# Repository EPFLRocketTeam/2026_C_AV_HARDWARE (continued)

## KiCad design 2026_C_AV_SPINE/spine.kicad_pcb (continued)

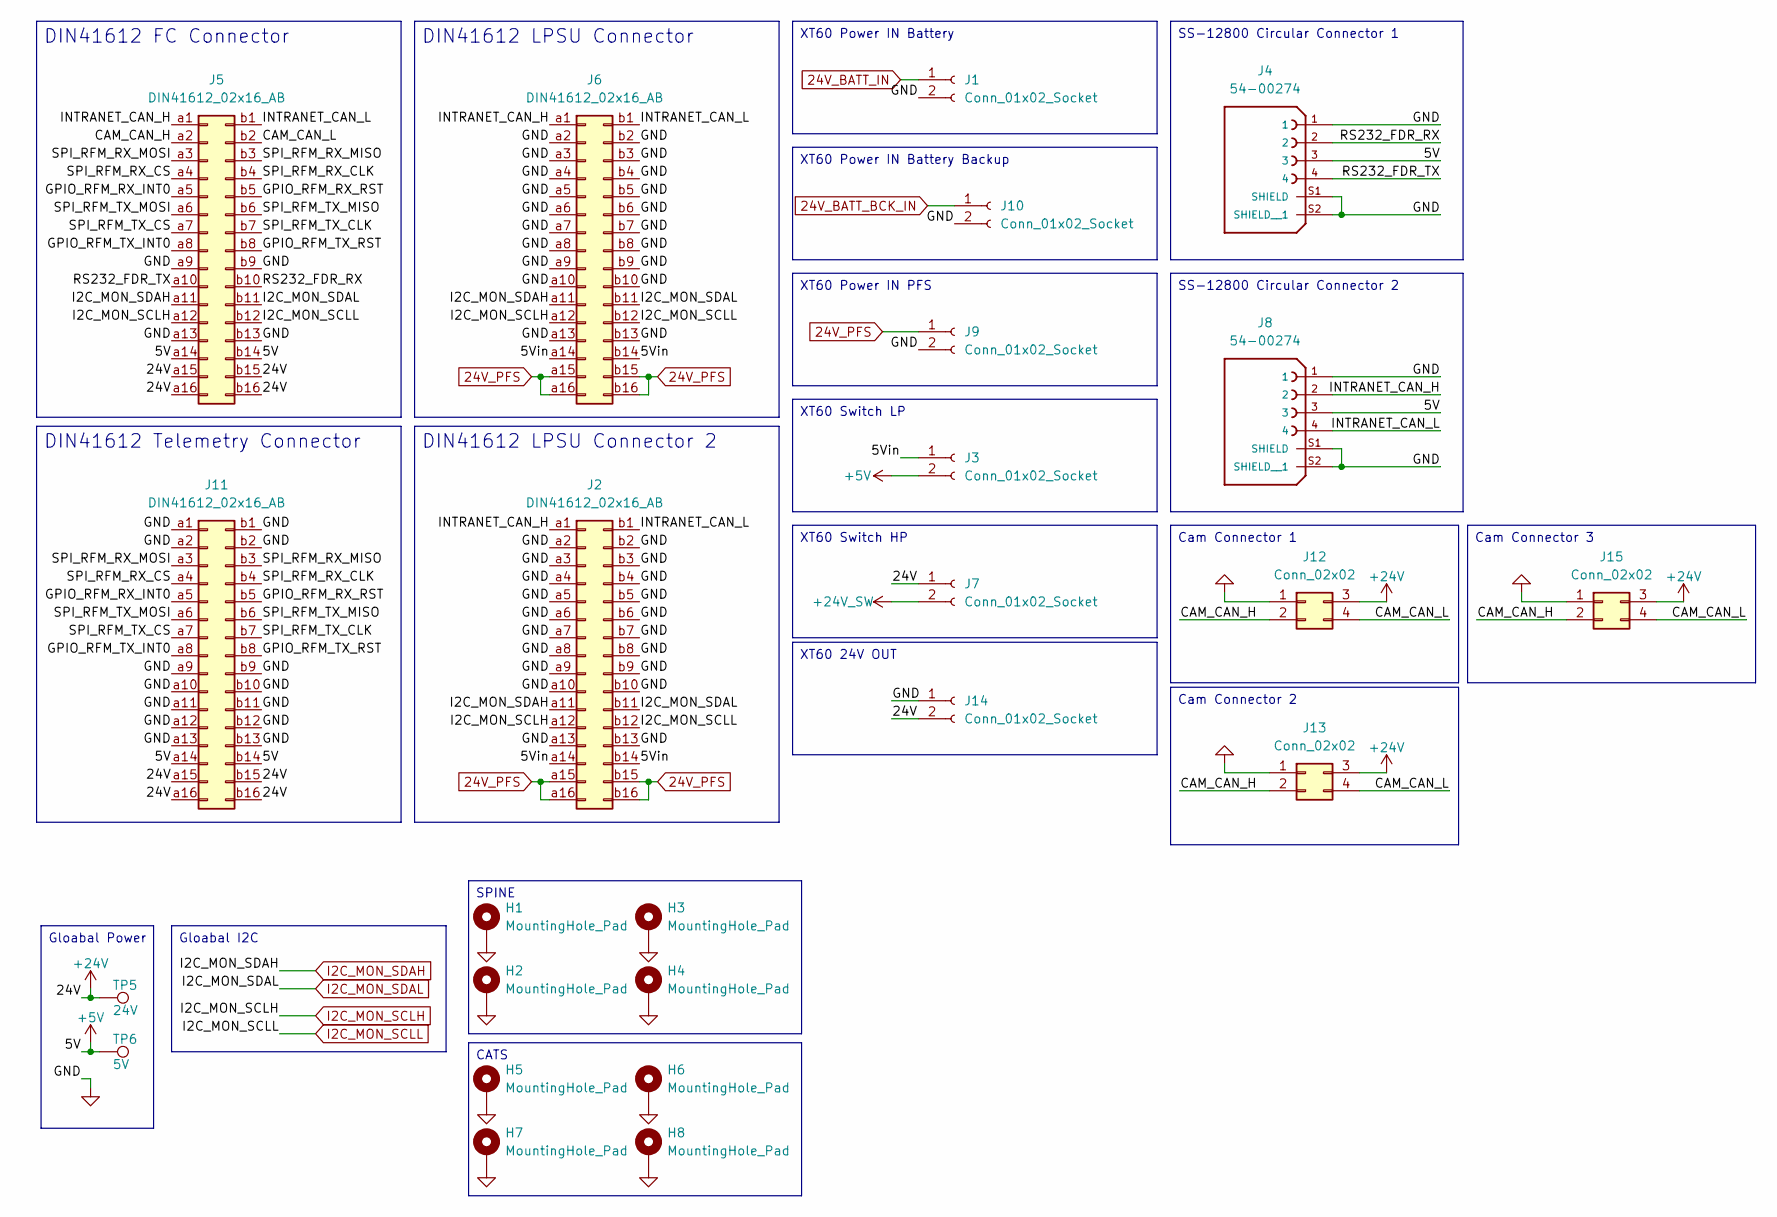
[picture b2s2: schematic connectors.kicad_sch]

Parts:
H1, H2, H3, H4, H5, H6, H7, H8: MountingHole_Pad; MountingHole_3.2mm_M3_Pad
J1, J3, J7, J9, J10, J14: Conn_01x02_Socket; AMASS_XT60IPW-M_1x03_P7.20mm_Horizontal
J2, J5, J6, J11: DIN41612_02x16_AB; DIN41612_B2_2x16_Female_Vertical_THT
J4, J8: 54-00274; TENSILITY_54-00274; PARTREV A
J12, J13, J15: Conn_02x02; SHDRRA4W55P200_2X2_665X640X630P
TP5: 24V; TestPoint_THTPad_D3.0mm_Drill1.5mm
TP6: 5V; TestPoint_THTPad_D3.0mm_Drill1.5mm

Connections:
24V_BATT_BCK_IN: J10.1; also elsewhere on the board
24V_BATT_IN: J1.1; also elsewhere on the board
24V_PFS: J2.a15, J2.a16, J2.b15, J2.b16, J6.a15, J6.a16, J6.b15, J6.b16, J9.1; also elsewhere on the board
+5V: J3.2, J4.3, J5.a14, J5.b14, J8.3, J11.a14, J11.b14, TP6.1; also elsewhere on the board
+24V: J5.a15, J5.a16, J5.b15, J5.b16, J7.1, J11.a15, J11.a16, J11.b15, J11.b16, J12.3, J13.3, J14.2, J15.3, TP5.1
+24V_SW: J7.2; also elsewhere on the board
/Connectors/5Vin: J2.a14, J2.b14, J3.1, J6.a14, J6.b14
/Connectors/CAM_CAN_H: J5.a2, J12.2, J13.2, J15.2
/Connectors/CAM_CAN_L: J5.b2, J12.4, J13.4, J15.4
/Connectors/GPIO_RFM_RX_INT0: J5.a5, J11.a5
/Connectors/GPIO_RFM_RX_RST: J5.b5, J11.b5
/Connectors/GPIO_RFM_TX_INT0: J5.a8, J11.a8
/Connectors/GPIO_RFM_TX_RST: J5.b8, J11.b8
/Connectors/INTRANET_CAN_H: J2.a1, J5.a1, J6.a1, J8.2
/Connectors/INTRANET_CAN_L: J2.b1, J5.b1, J6.b1, J8.4
/Connectors/RS232_FDR_RX: J4.2, J5.b10
/Connectors/RS232_FDR_TX: J4.4, J5.a10
/Connectors/SPI_RFM_RX_CLK: J5.b4, J11.b4
/Connectors/SPI_RFM_RX_CS: J5.a4, J11.a4
/Connectors/SPI_RFM_RX_MISO: J5.b3, J11.b3
/Connectors/SPI_RFM_RX_MOSI: J5.a3, J11.a3
/Connectors/SPI_RFM_TX_CLK: J5.b7, J11.b7
/Connectors/SPI_RFM_TX_CS: J5.a7, J11.a7
/Connectors/SPI_RFM_TX_MISO: J5.b6, J11.b6
/Connectors/SPI_RFM_TX_MOSI: J5.a6, J11.a6
GND: H1.1, H2.1, H3.1, H4.1, H5.1, H6.1, H7.1, H8.1, J1.2, J2.a2, J2.a3, J2.a4, J2.a5, J2.a6, J2.a7, J2.a8, J2.a9, J2.a10, J2.a13, J2.b2, J2.b3, J2.b4, J2.b5, J2.b6, J2.b7, J2.b8, J2.b9, J2.b10, J2.b13, J4.1, J4.S1 (SHIELD), J4.S2 (SHIELD__1), J5.a9, J5.a13, J5.b9, J5.b13, J6.a2, J6.a3, J6.a4, J6.a5, J6.a6, J6.a7, J6.a8, J6.a9, J6.a10, J6.a13, J6.b2, J6.b3, J6.b4, J6.b5, J6.b6, J6.b7, J6.b8, J6.b9, J6.b10, J6.b13, J8.1, J8.S1 (SHIELD), J8.S2 (SHIELD__1), J9.2, J10.2, J11.a1, J11.a2, J11.a9, J11.a10, J11.a11, J11.a12, J11.a13, J11.b1, J11.b2, J11.b9, J11.b10, J11.b11, J11.b12, J11.b13, J12.1, J13.1, J14.1, J15.1; also elsewhere on the board
I2C_MON_SCLH: J2.a12, J5.a12, J6.a12; also elsewhere on the board
I2C_MON_SCLL: J2.b12, J5.b12, J6.b12; also elsewhere on the board
I2C_MON_SDAH: J2.a11, J5.a11, J6.a11; also elsewhere on the board
I2C_MON_SDAL: J2.b11, J5.b11, J6.b11; also elsewhere on the board

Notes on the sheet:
SPINE
XT60 Switch HP
DIN41612 LPSU Connector 2
Cam Connector 3
Cam Connector 1
DIN41612 LPSU Connector
DIN41612 Telemetry Connector
XT60 Power IN Battery Backup
Gloabal I2C
CATS
SS-12800 Circular Connector 2
XT60 24V OUT
SS-12800 Circular Connector 1
DIN41612 FC Connector
XT60 Power IN Battery
Cam Connector 2
XT60 Switch LP
XT60 Power IN PFS
Gloabal Power

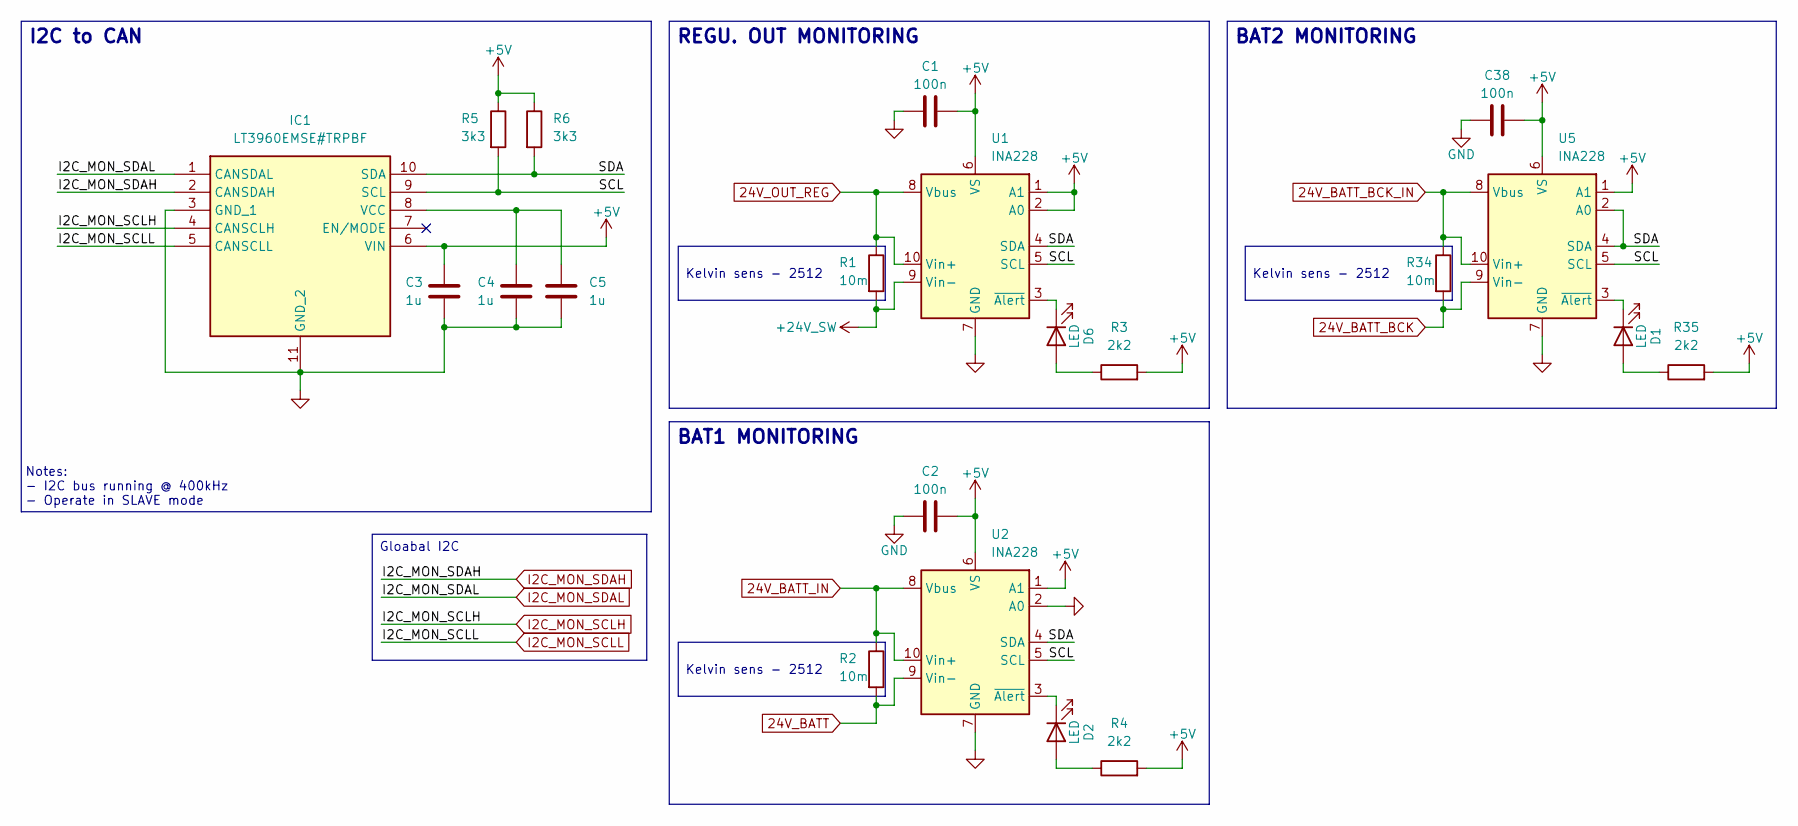
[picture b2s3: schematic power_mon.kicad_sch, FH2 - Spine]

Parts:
C1, C2, C38: 100n; C_0603_1608Metric
C3, C4, C5: 1u; C_0603_1608Metric
D1, D2, D6: LED; LED_0603_1608Metric
IC1: LT3960EMSE#TRPBF; SOP50P490X110-11N; Mouser Part Number 584-LT3960EMSE#TRPBF
R1, R2, R34: 10m; R_2512_6332Metric
R3, R4, R35: 2k2; R_0603_1608Metric
R5, R6: 3k3; R_0603_1608Metric
U1, U2, U5: INA228; VSSOP-10_3x3mm_P0.5mm

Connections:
24V_BATT: R2.2, U2.9 (Vin-); also elsewhere on the board
24V_BATT_BCK: R34.2, U5.9 (Vin-); also elsewhere on the board
24V_BATT_BCK_IN: R34.1, U5.8 (Vbus), U5.10 (Vin+); also elsewhere on the board
24V_BATT_IN: R2.1, U2.8 (Vbus), U2.10 (Vin+); also elsewhere on the board
24V_OUT_REG: R1.1, U1.8 (Vbus), U1.10 (Vin+); also elsewhere on the board
+5V: C1.2, C2.2, C3.1, C38.2, IC1.6 (VIN), R3.2, R4.2, R5.1, R6.1, R35.2, U1.1 (A1), U1.2 (A0), U1.6 (VS), U2.1 (A1), U2.6 (VS), U5.1 (A1), U5.6 (VS); also elsewhere on the board
+24V_SW: R1.2, U1.9 (Vin-); also elsewhere on the board
/Power/Monitoring/SCL: IC1.9 (SCL), R5.2, U1.5 (SCL), U2.5 (SCL), U5.5 (SCL)
/Power/Monitoring/SDA: IC1.10 (SDA), R6.2, U1.4 (SDA), U2.4 (SDA), U5.2 (A0), U5.4 (SDA)
GND: C1.1, C2.1, C3.2, C4.1, C5.2, C38.1, IC1.3 (GND_1), IC1.11 (GND_2), U1.7 (GND), U2.2 (A0), U2.7 (GND), U5.7 (GND); also elsewhere on the board
I2C_MON_SCLH: IC1.4 (CANSCLH); also elsewhere on the board
I2C_MON_SCLL: IC1.5 (CANSCLL); also elsewhere on the board
I2C_MON_SDAH: IC1.2 (CANSDAH); also elsewhere on the board
I2C_MON_SDAL: IC1.1 (CANSDAL); also elsewhere on the board
unnamed: D1.2 (A), R35.1
unnamed: D1.1 (K), U5.3 (~Alert)
unnamed: D2.2 (A), R4.1
unnamed: D2.1 (K), U2.3 (~Alert)
unnamed: D6.2 (A), R3.1
unnamed: D6.1 (K), U1.3 (~Alert)
unnamed: C4.2, C5.1, IC1.8 (VCC)

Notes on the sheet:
Notes: - I2C bus running @ 400kHz - Operate in SLAVE mode
I2C to CAN
BAT2 MONITORING
REGU. OUT MONITORING
Kelvin sens - 2512
BAT1 MONITORING
Gloabal I2C

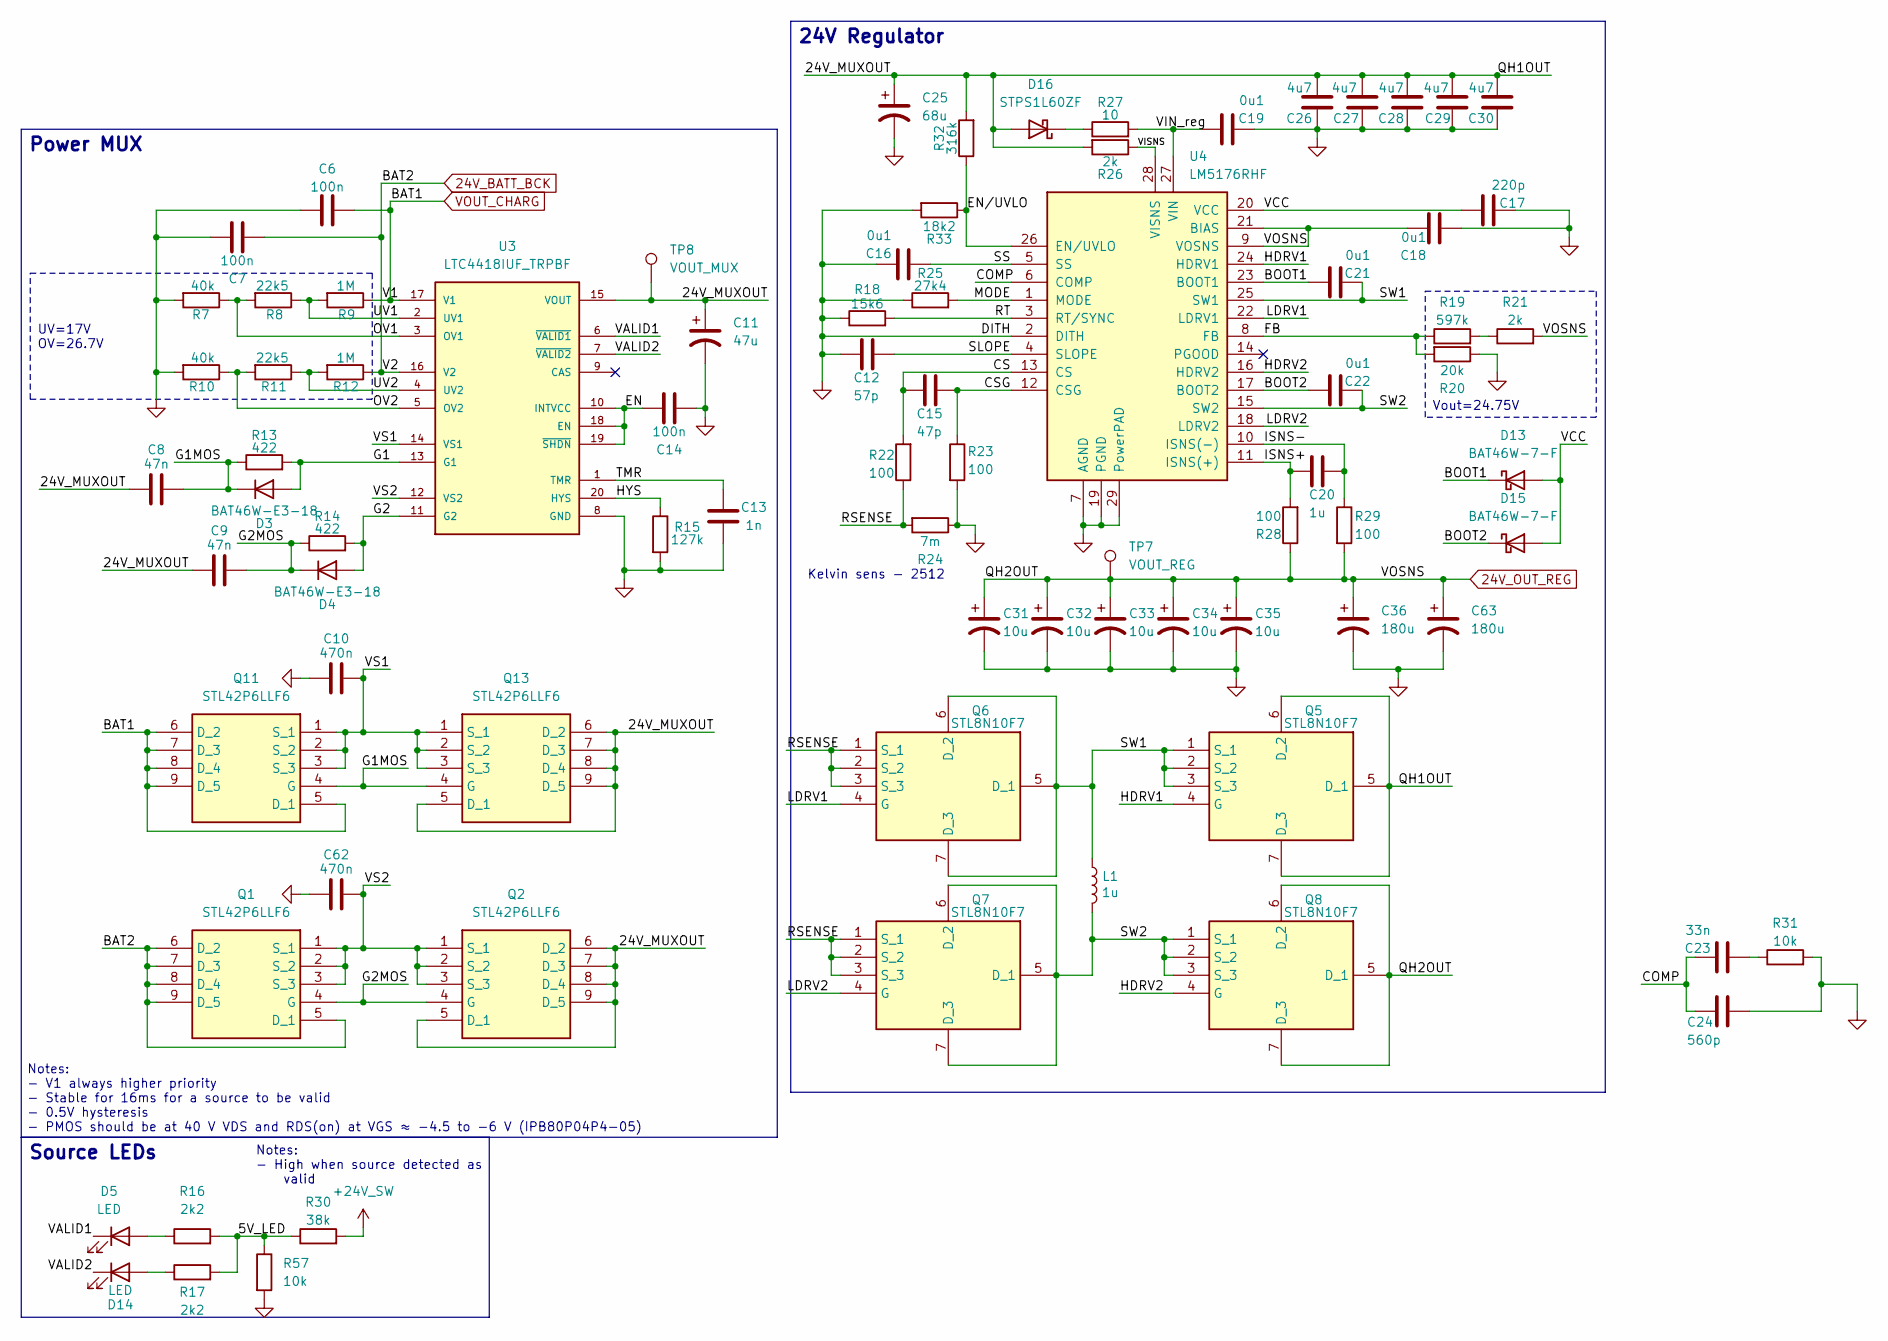
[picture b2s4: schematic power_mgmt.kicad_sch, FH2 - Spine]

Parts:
C6, C7, C14: 100n; C_0603_1608Metric
C8, C9: 47n; C_0603_1608Metric
C10, C62: 470n; C_0603_1608Metric
C11: 47u; CP_Elec_6.3x9.9
C12: 57p; C_0603_1608Metric
C13: 1n; C_0603_1608Metric
C15: 47p; C_0603_1608Metric
C16, C18, C19, C21, C22: 0u1; C_0603_1608Metric
C17: 220p; C_0603_1608Metric
C20: 1u; C_0603_1608Metric
C23: 33n; C_0603_1608Metric
C24: 560p; C_0603_1608Metric
C25: 68u; CP_Elec_6.3x5.9
C26, C27, C28, C29, C30: 4u7; C_0603_1608Metric
C31, C32, C33, C34, C35: 10u; C_Elec_4x5.4
C36, C63: 180u; CP_Elec_10x10.5
D3, D4: BAT46W-E3-18; D_SOD-123
D5, D14: LED; LED_0603_1608Metric
D13, D15: BAT46W-7-F; D_SOD-123
D16: STPS1L60ZF; D_SOD-123
L1: 1u; L_12x12mm_H6mm
Q1, Q2, Q11, Q13: STL42P6LLF6; Mouser Part Number 511-STL42P6LLF6
Q5, Q6, Q7, Q8: STL8N10F7; Mouser Part Number 511-STL8N10F7
R7, R10: 40k; R_0603_1608Metric
R8, R11: 22k5; R_0603_1608Metric
R9, R12: 1M; R_0603_1608Metric
R13, R14: 422; R_0603_1608Metric
R15: 127k; R_0603_1608Metric
R16, R17: 2k2; R_0603_1608Metric
R18: 15k6; R_0603_1608Metric
R19: 597k; R_0603_1608Metric
R20: 20k; R_0603_1608Metric
R21, R26: 2k; R_0603_1608Metric
R22, R23, R28, R29: 100; R_0603_1608Metric
R24: 7m; R_2512_6332Metric
R25: 27k4; R_0603_1608Metric
R27: 10; R_0603_1608Metric
R30: 38k; R_0603_1608Metric
R31, R57: 10k; R_0603_1608Metric
R32: 316k; R_0603_1608Metric
R33: 18k2; R_0603_1608Metric
TP7: VOUT_REG; TestPoint_Pad_D2.0mm
TP8: VOUT_MUX; TestPoint_Pad_D1.5mm
U3: LTC4418IUF_TRPBF; QFN-20-1EP_4x4mm_P0.5mm_EP2.5x2.5mm_ThermalVias; PARTREV A
U4: LM5176RHF; VQFN-28-1EP_4x5mm_P0.5mm_EP2.55x3.55mm_ThermalVias

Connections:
24V_BATT_BCK: C7.1, Q1.5 (D_1), Q1.6 (D_2), Q1.7 (D_3), Q1.8 (D_4), Q1.9 (D_5), R12.1, U3.16 (V2); also elsewhere on the board
24V_OUT_REG: C18.1, C31.1, C32.1, C33.1, C34.1, C35.1, C36.1, C63.1, Q8.5 (D_1), Q8.6 (D_2), Q8.7 (D_3), R21.2, R28.1, R29.2, TP7.1, U4.9 (VOSNS), U4.21 (BIAS); also elsewhere on the board
+24V_SW: R30.2; also elsewhere on the board
/Power/Management/5V_LED: R16.2, R17.2, R30.1, R57.1
/Power/Management/24V_MUXOUT: C8.1, C9.1, C11.1, C25.1, C26.2, C27.2, C28.2, C29.2, C30.2, D16.2 (A), Q2.5 (D_1), Q2.6 (D_2), Q2.7 (D_3), Q2.8 (D_4), Q2.9 (D_5), Q5.5 (D_1), Q5.6 (D_2), Q5.7 (D_3), Q13.5 (D_1), Q13.6 (D_2), Q13.7 (D_3), Q13.8 (D_4), Q13.9 (D_5), R26.2, R32.2, TP8.1, U3.15 (VOUT)
/Power/Management/BOOT1: C21.1, D13.1 (K), U4.23 (BOOT1)
/Power/Management/BOOT2: C22.1, D15.1 (K), U4.17 (BOOT2)
/Power/Management/COMP: C23.1, C24.2, U4.6 (COMP)
/Power/Management/CS: C15.2, R22.2, U4.13 (CS)
/Power/Management/CSG: C15.1, R23.1, U4.12 (CSG)
/Power/Management/EN: C14.2, U3.10 (INTVCC), U3.18 (EN), U3.19 (~SHDN)
/Power/Management/EN/UVLO: R32.1, R33.1, U4.26 (EN/UVLO)
/Power/Management/FB: R19.1, R20.2, U4.8 (FB)
/Power/Management/G1: D3.2 (A), R13.2, U3.13 (G1)
/Power/Management/G1MOS: C8.2, D3.1 (K), Q11.4 (G), Q13.4 (G), R13.1
/Power/Management/G2: D4.2 (A), R14.2, U3.11 (G2)
/Power/Management/G2MOS: C9.2, D4.1 (K), Q1.4 (G), Q2.4 (G), R14.1
/Power/Management/HDRV1: Q5.4 (G), U4.24 (HDRV1)
/Power/Management/HDRV2: Q8.4 (G), U4.16 (HDRV2)
/Power/Management/HYS: R15.1, U3.20 (HYS)
/Power/Management/ISNS+: C20.2, R28.2, U4.11 (ISNS(+))
/Power/Management/ISNS-: C20.1, R29.1, U4.10 (ISNS(-))
/Power/Management/LDRV1: Q6.4 (G), U4.22 (LDRV1)
/Power/Management/LDRV2: Q7.4 (G), U4.18 (LDRV2)
/Power/Management/MODE: R25.2, U4.1 (MODE)
/Power/Management/OV1: R7.1, R8.2, U3.3 (OV1)
/Power/Management/OV2: R10.1, R11.2, U3.5 (OV2)
/Power/Management/RSENSE: Q6.1 (S_1), Q6.2 (S_2), Q6.3 (S_3), Q7.1 (S_1), Q7.2 (S_2), Q7.3 (S_3), R22.1, R24.2
/Power/Management/RT: R18.2, U4.3 (RT/SYNC)
/Power/Management/SLOPE: C12.1, U4.4 (SLOPE)
/Power/Management/SS: C16.2, U4.5 (SS)
/Power/Management/SW1: C21.2, L1.1, Q5.1 (S_1), Q5.2 (S_2), Q5.3 (S_3), Q6.5 (D_1), Q6.6 (D_2), Q6.7 (D_3), U4.25 (SW1)
/Power/Management/SW2: C22.2, L1.2, Q7.5 (D_1), Q7.6 (D_2), Q7.7 (D_3), Q8.1 (S_1), Q8.2 (S_2), Q8.3 (S_3), U4.15 (SW2)
/Power/Management/TMR: C13.1, U3.1 (TMR)
/Power/Management/UV1: R8.1, R9.2, U3.2 (UV1)
/Power/Management/UV2: R11.1, R12.2, U3.4 (UV2)
/Power/Management/VALID1: D5.1 (K), U3.6 (~VALID1)
/Power/Management/VALID2: D14.1 (K), U3.7 (~VALID2)
/Power/Management/VCC: C17.1, D13.2 (A), D15.2 (A), U4.20 (VCC)
/Power/Management/VIN_reg: C19.1, R27.2, U4.27 (VIN)
/Power/Management/VISNS: R26.1, U4.28 (VISNS)
/Power/Management/VS1: C10.2, Q11.1 (S_1), Q11.2 (S_2), Q11.3 (S_3), Q13.1 (S_1), Q13.2 (S_2), Q13.3 (S_3), U3.14 (VS1)
/Power/Management/VS2: C62.2, Q1.1 (S_1), Q1.2 (S_2), Q1.3 (S_3), Q2.1 (S_1), Q2.2 (S_2), Q2.3 (S_3), U3.12 (VS2)
GND: C6.1, C7.2, C10.1, C11.2, C12.2, C13.2, C14.1, C16.1, C17.2, C18.2, C19.2, C24.1, C25.2, C26.1, C27.1, C28.1, C29.1, C30.1, C31.2, C32.2, C33.2, C34.2, C35.2, C36.2, C62.1, C63.2, R7.2, R10.2, R15.2, R18.1, R20.1, R23.2, R24.1, R25.1, R31.2, R33.2, R57.2, U3.8 (GND), U3.21 (GND), U4.2 (DITH), U4.7 (AGND), U4.19 (PGND), U4.29 (PowerPAD); also elsewhere on the board
unnamed: C23.2, R31.1
unnamed: D5.2 (A), R16.1
unnamed: D14.2 (A), R17.1
unnamed: D16.1 (K), R27.1
unnamed: R19.2, R21.1
VOUT_CHARG: C6.2, Q11.5 (D_1), Q11.6 (D_2), Q11.7 (D_3), Q11.8 (D_4), Q11.9 (D_5), R9.1, U3.17 (V1); also elsewhere on the board

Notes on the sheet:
Notes: - High when source detected as valid
Kelvin sens - 2512
Notes: - V1 always higher priority - Stable for 16ms for a source to be valid - 0.5V hysteresis - PMOS should be at 40 V VDS and RDS(on) at VGS ≈ −4.5 to −6 V (IPB80P04P4-05)
24V Regulator
Power MUX
Source LEDs
UV=17V OV=26.7V
Vout=24.75V

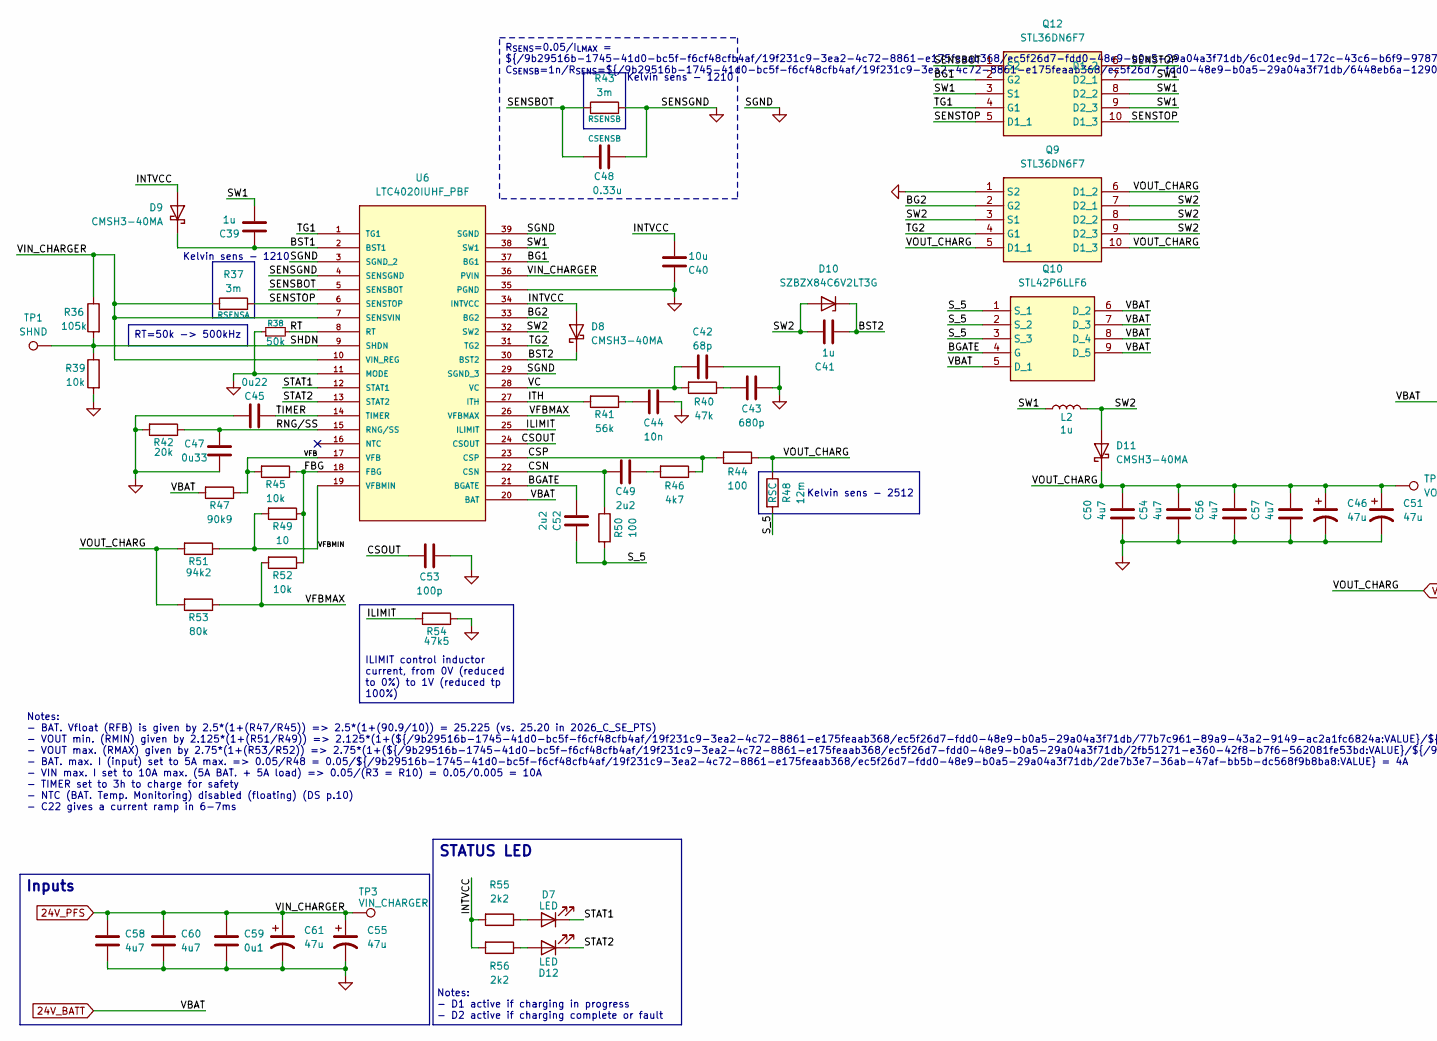
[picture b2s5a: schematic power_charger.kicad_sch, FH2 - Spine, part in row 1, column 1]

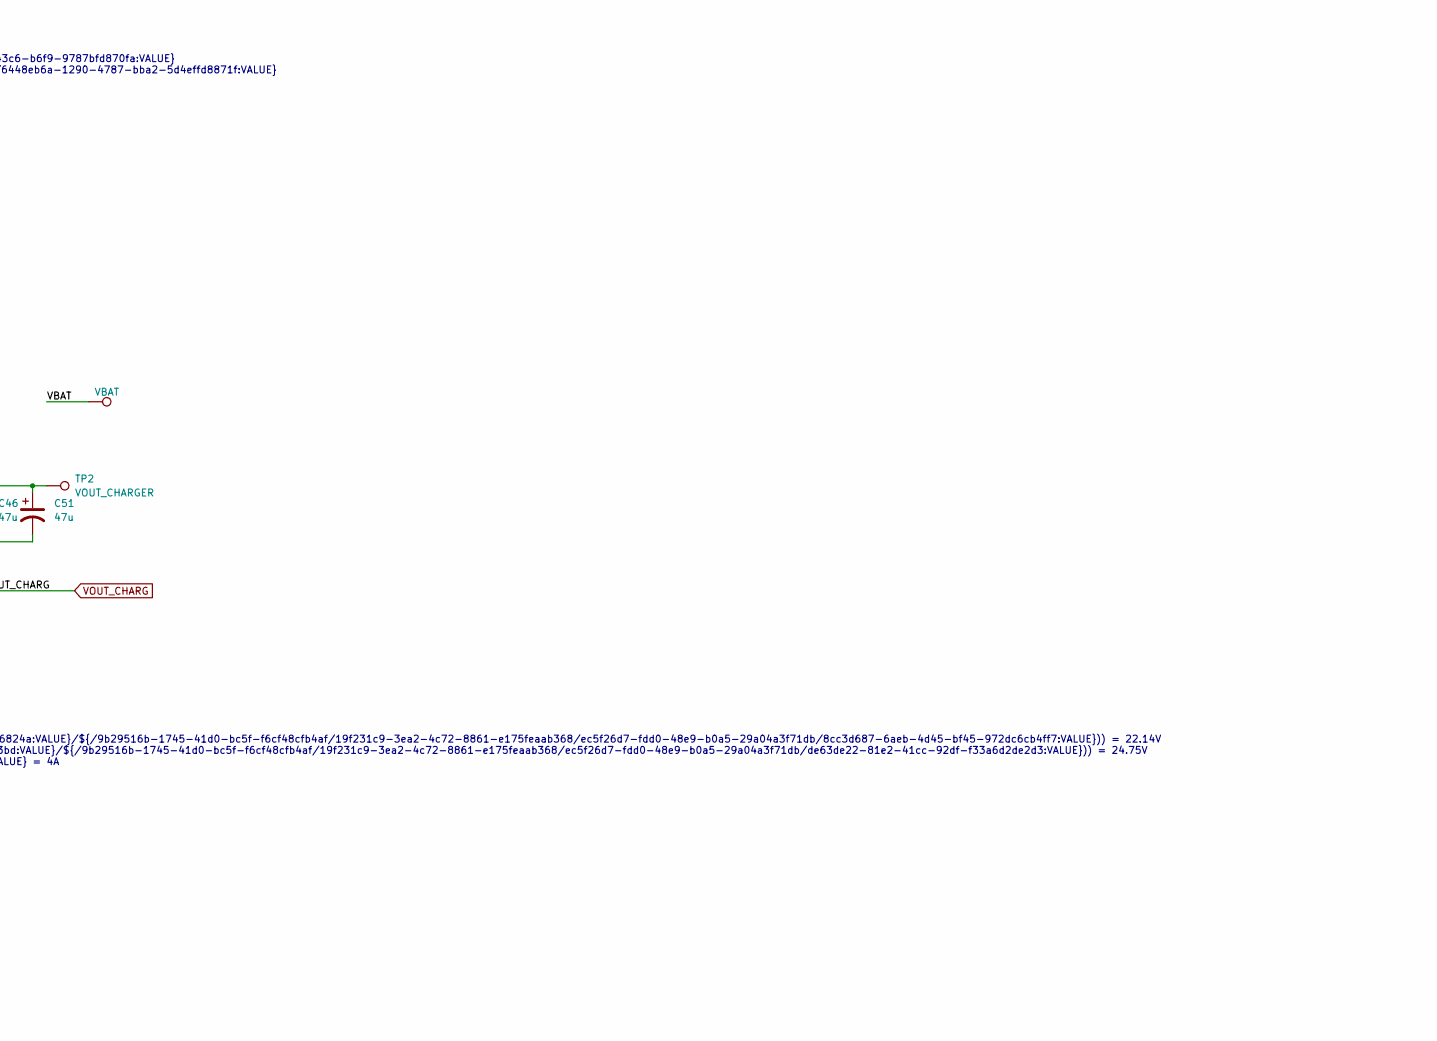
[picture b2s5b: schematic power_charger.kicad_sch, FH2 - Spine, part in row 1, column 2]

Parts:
C39, C41: 1u; C_0603_1608Metric
C40: 10u; C_Elec_4x5.4
C42: 68p; C_0603_1608Metric
C43: 680p; C_0603_1608Metric
C44: 10n; C_0603_1608Metric
C45: 0u22; C_0603_1608Metric
C46, C51, C55, C61: 47u; CP_Elec_6.3x9.9
C47: 0u33; C_0603_1608Metric
C48: 0.33u; C_0603_1608Metric
C49, C52: 2u2; C_0603_1608Metric
C50, C54, C56, C57, C58, C60: 4u7; C_0603_1608Metric
C53: 100p; C_0603_1608Metric
C59: 0u1; C_0603_1608Metric
D7, D12: LED; LED_0603_1608Metric
D8, D9, D11: CMSH3-40MA; D_SMA
D10: SZBZX84C6V2LT3G; SOT-23-3
L2: 1u; L_10.4x10.4_H4.8
Q9, Q12: STL36DN6F7; Mouser Part Number 511-STL36DN6F7
Q10: STL42P6LLF6; Mouser Part Number 511-STL42P6LLF6
R36: 105k; R_0603_1608Metric
R37, R43: 3m; R_1210_3225Metric
R38: 50k; R_0603_1608Metric
R39, R45, R52: 10k; R_0603_1608Metric
R40: 47k; R_0603_1608Metric
R41: 56k; R_0603_1608Metric
R42: 20k; R_0603_1608Metric
R44, R50: 100; R_0603_1608Metric
R46: 4k7; R_0603_1608Metric
R47: 90k9; R_0603_1608Metric
R48: 12m; R_2512_6332Metric
R49: 10; R_0603_1608Metric
R51: 94k2; R_0603_1608Metric
R53: 80k; R_0603_1608Metric
R54: 47k5; R_0603_1608Metric
R55, R56: 2k2; R_0603_1608Metric
TP1: SHND; TestPoint_Pad_D2.0mm
TP2: VOUT_CHARGER; TestPoint_Pad_D2.0mm
TP3: VIN_CHARGER; TestPoint_Pad_D2.0mm
TP4: VBAT; TestPoint_Pad_D2.0mm
U6: LTC4020IUHF_PBF; QFN-38-1EP_4x6mm_P0.4mm_EP2.65x4.65mm_ThermalVias; MANUFACTURER_PART_NUMBER ltc4020iuhf#pbf

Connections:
24V_BATT: Q10.5 (D_1), Q10.6 (D_2), Q10.7 (D_3), Q10.8 (D_4), Q10.9 (D_5), R47.2, TP4.1, U6.20 (BAT); also elsewhere on the board
24V_PFS: C55.1, C58.1, C59.1, C60.1, C61.1, R36.1, R37.1, TP3.1, U6.7 (SENSVIN), U6.10 (VIN_REG), U6.36 (PVIN); also elsewhere on the board
/Power/Charger/BG1: Q12.2 (G2), U6.37 (BG1)
/Power/Charger/BG2: Q9.2 (G2), U6.33 (BG2)
/Power/Charger/BGATE: C52.1, Q10.4 (G), U6.21 (BGATE)
/Power/Charger/BST1: C39.1, D9.1 (K), U6.2 (BST1)
/Power/Charger/BST2: C41.2, D8.1 (K), D10.1 (K), U6.30 (BST2)
/Power/Charger/CSN: C49.1, R50.1, U6.22 (CSN)
/Power/Charger/CSOUT: C53.1, U6.24 (CSOUT)
/Power/Charger/CSP: R44.2, R46.1, U6.23 (CSP)
/Power/Charger/FBG: R45.1, R49.1, R52.1, U6.18 (FBG)
/Power/Charger/ILIMIT: R54.2, U6.25 (ILIMIT)
/Power/Charger/INTVCC: C40.2, D8.2 (A), D9.2 (A), R55.2, R56.2, U6.34 (INTVCC)
/Power/Charger/ITH: R41.2, U6.27 (ITH)
/Power/Charger/RNG/SS: C47.1, R42.1, U6.15 (RNG/SS)
/Power/Charger/RT: R38.2, U6.8 (RT)
/Power/Charger/SENSBOT: C48.1, Q12.1 (S2), R43.1, U6.5 (SENSBOT)
/Power/Charger/SENSTOP: Q12.5 (D1_1), Q12.6 (D1_2), Q12.10 (D1_3), R37.2, U6.6 (SENSTOP)
/Power/Charger/SHDN: R36.2, R39.1, TP1.1, U6.9 (SHDN)
/Power/Charger/STAT1: D7.1 (K), U6.12 (STAT1)
/Power/Charger/STAT2: D12.1 (K), U6.13 (STAT2)
/Power/Charger/SW1: C39.2, L2.1, Q12.3 (S1), Q12.7 (D2_1), Q12.8 (D2_2), Q12.9 (D2_3), U6.38 (SW1)
/Power/Charger/SW2: C41.1, D10.2 (A), D11.2 (A), L2.2, Q9.3 (S1), Q9.7 (D2_1), Q9.8 (D2_2), Q9.9 (D2_3), U6.32 (SW2)
/Power/Charger/S_5: C52.2, Q10.1 (S_1), Q10.2 (S_2), Q10.3 (S_3), R48.2, R50.2
/Power/Charger/TG1: Q12.4 (G1), U6.1 (TG1)
/Power/Charger/TG2: Q9.4 (G1), U6.31 (TG2)
/Power/Charger/TIMER: C45.1, U6.14 (TIMER)
/Power/Charger/VC: C42.1, R40.2, U6.28 (VC)
/Power/Charger/VFB: R45.2, R47.1, U6.17 (VFB)
/Power/Charger/VFBMAX: R52.2, R53.1, U6.26 (VFBMAX)
/Power/Charger/VFBMIN: R49.2, R51.1, U6.19 (VFBMIN)
GND: C40.1, C42.2, C43.2, C44.2, C45.2, C46.2, C47.2, C48.2, C50.2, C51.2, C53.2, C54.2, C55.2, C56.2, C57.2, C58.2, C59.2, C60.2, C61.2, Q9.1 (S2), R38.1, R39.2, R42.2, R43.2, R54.1, U6.3 (SGND_2), U6.4 (SENSGND), U6.11 (MODE), U6.29 (SGND_3), U6.35 (PGND), U6.39 (SGND); also elsewhere on the board
unnamed: C43.1, R40.1
unnamed: C44.1, R41.1
unnamed: C49.2, R46.2
unnamed: D7.2 (A), R55.1
unnamed: D12.2 (A), R56.1
VOUT_CHARG: C46.1, C50.1, C51.1, C54.1, C56.1, C57.1, D11.1 (K), Q9.5 (D1_1), Q9.6 (D1_2), Q9.10 (D1_3), R44.1, R48.1, R51.2, R53.2, TP2.1; also elsewhere on the board

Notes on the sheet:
Notes: - BAT. Vfloat (RFB) is given by 2.5*(1+(R47/R45)) => 2.5*(1+(90.9/10)) = 25.225 (vs. 25.20 in 2026_C_SE_PTS) - VOUT min. (RMIN) given by 2.125*(1+(R51/R49)) => 2.125*(1+(${/9b29516b-1745-41d0-bc5f-f6cf48cfb4af/19f231c9-3ea2-4c72-8861-e175feaab368/ec5f26d7-fdd0-48e9-b0a5-29a04a3f71db/77b7c961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
Notes: - D1 active if charging in progress - D2 active if charging complete or fault
Kelvin sens - 1210
STATUS LED
RT=50k -> 500kHz
Inputs
R_{SENS}=0.05/I_{LMAX} = ${/9b29516b-1745-41d0-bc5f-f6cf48cfb4af/19f231c9-3ea2-4c72-8861-e175feaab368/ec5f26d7-fdd0-48e9-b0a5-29a04a3f71db/6c01ec9d-172c-43c6-b6f9-9787bfd870fa:VALUE} C_{SENSB}=1n/R_{SENS}=${/9b29516b-1745-41d0-bc5f-f6cf48cfb4af/19f231c9-3ea2-4c72-8861-e175feaab368/ec5f26d7-fdd0-48e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
ILIMIT control inductor current, from 0V (reduced to 0%) to 1V (reduced tp 100%)
Kelvin sens - 2512

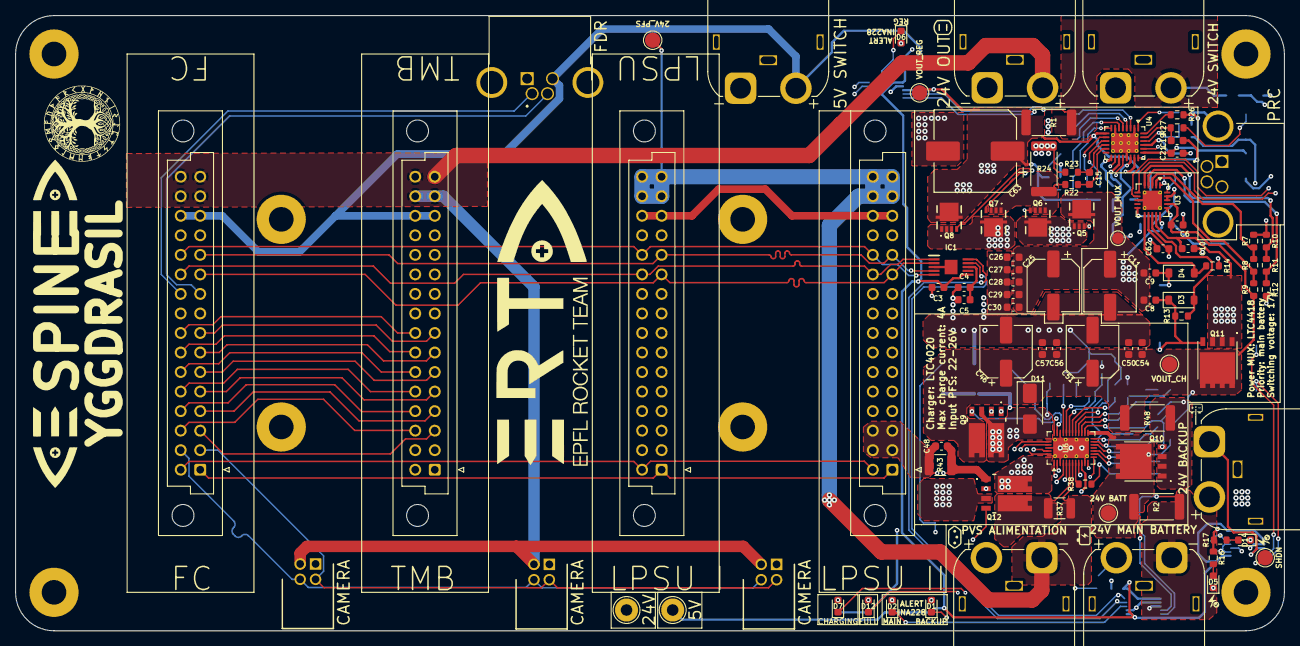
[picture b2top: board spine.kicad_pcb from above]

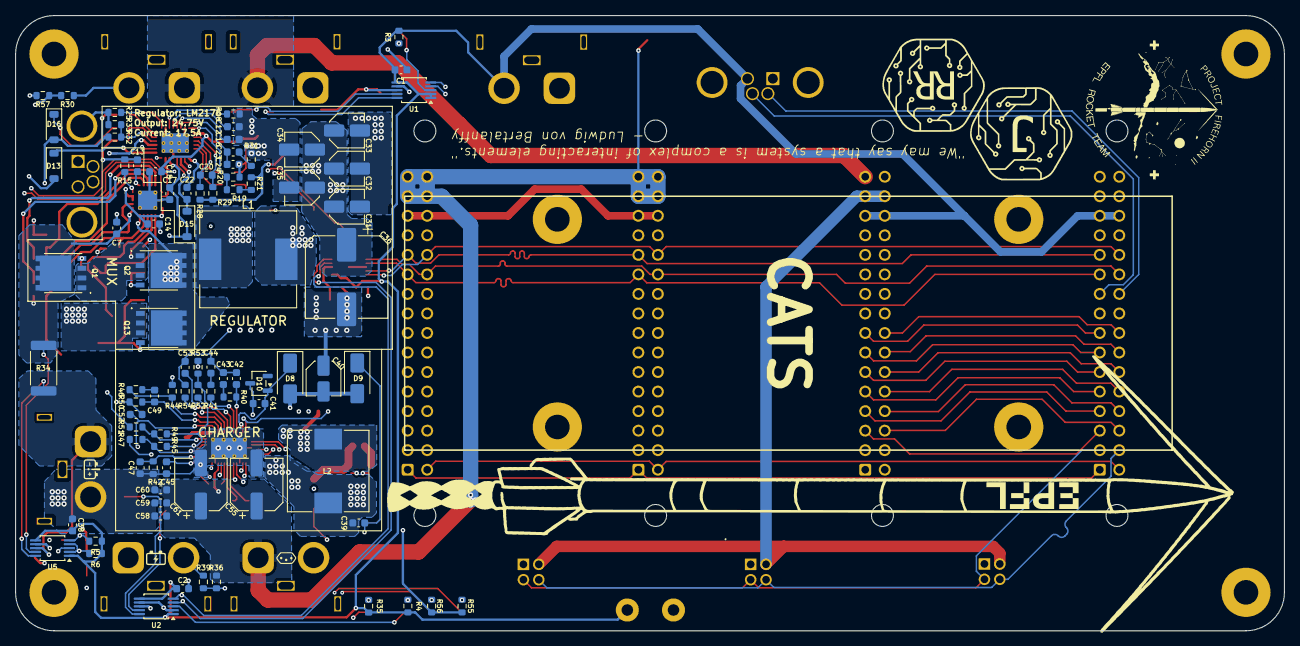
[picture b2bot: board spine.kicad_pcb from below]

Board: 4 copper layers, 165.0 x 80.0 mm, 186 parts (87 on the bottom side), 122 nets.

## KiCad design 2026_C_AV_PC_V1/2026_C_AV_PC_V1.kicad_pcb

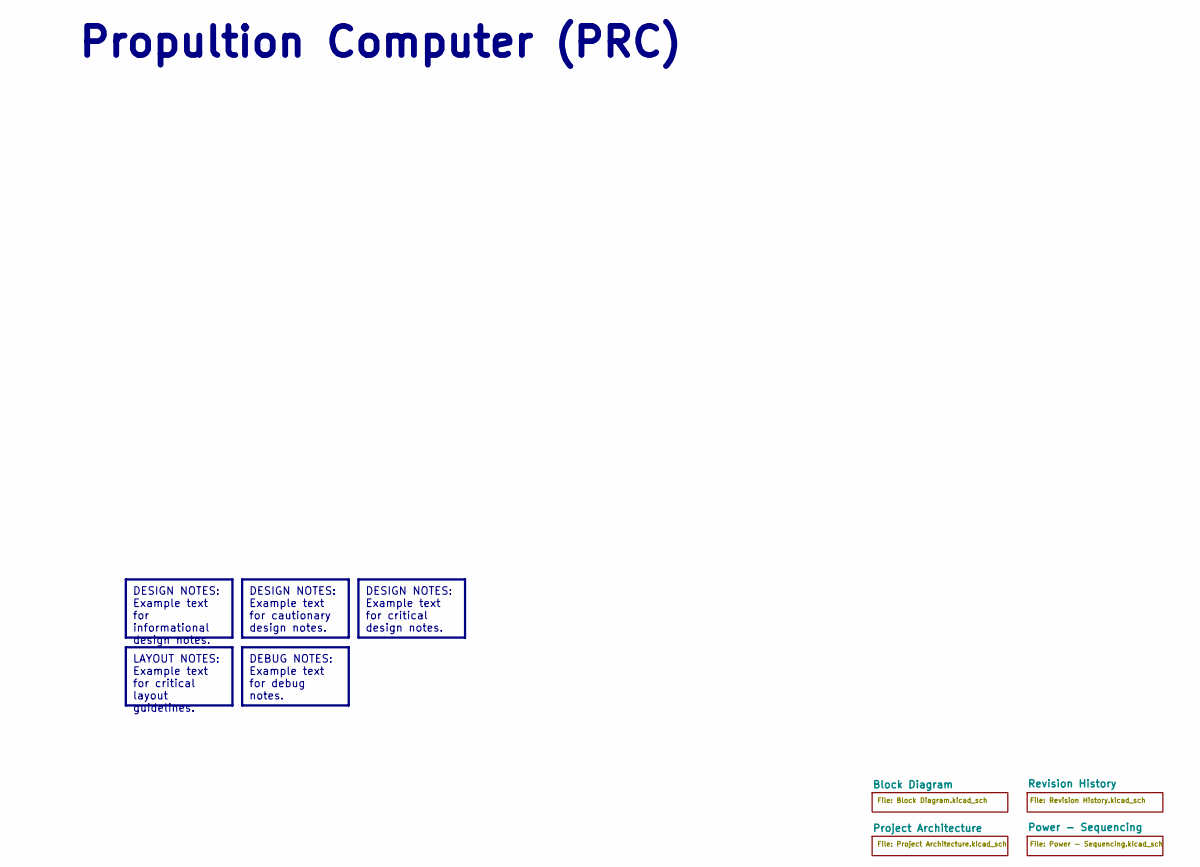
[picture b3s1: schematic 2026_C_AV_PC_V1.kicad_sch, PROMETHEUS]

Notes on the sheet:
Propultion Computer (PRC)
DESIGN NOTES: Example text for informational design notes.
DESIGN NOTES: Example text for critical design notes.
DESIGN NOTES: Example text for cautionary design notes.
DEBUG NOTES: Example text for debug notes.
LAYOUT NOTES: Example text for critical layout guidelines.

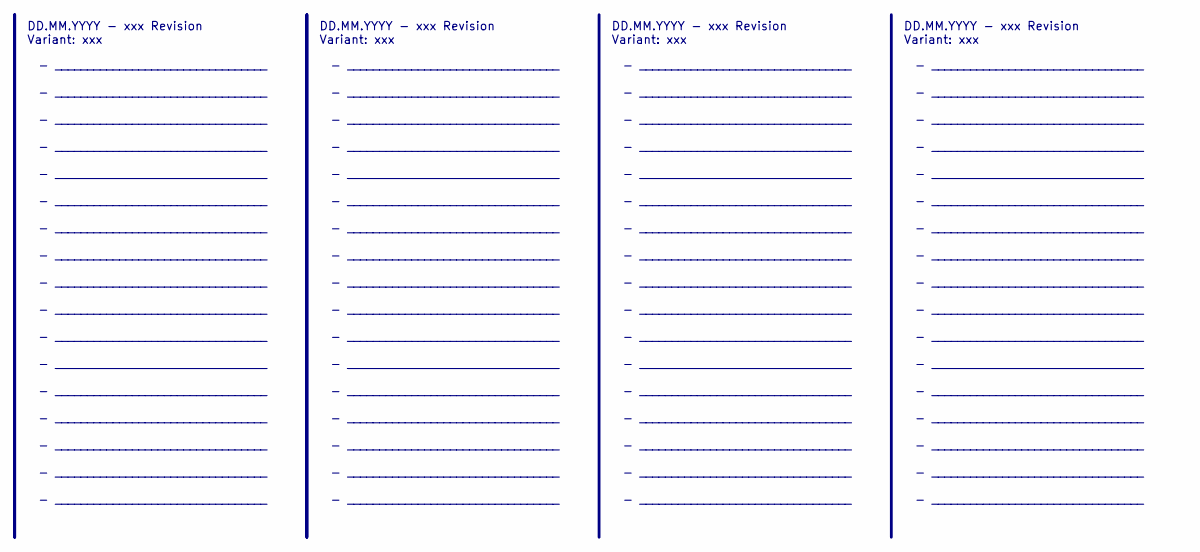
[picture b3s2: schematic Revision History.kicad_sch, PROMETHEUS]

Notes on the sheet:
- _________________________________ - _________________________________ - _________________________________ - _________________________________ - _________________________________ - _________________________________ - _________________________________ - _________________________________ - _________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
DD.MM.YYYY - xxx Revision Variant: xxx
